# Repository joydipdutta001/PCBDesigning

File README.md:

# PCB Designs ✨✨✨❤
**I am providing some of my work with cad softwares to design PCBs.**
<br></br>
**Software used : ✔ Autodesk EAGLE Educational.**
<br></br>

# Project-1: My own Arduino Designing 😎
[Click Me for Gerber Files](https://github.com/joydipdutta001/PCBDesigning/tree/master/P1-Arduino%20Replica/version1_2020-08-09)
<br></br>
<figure>
    <h3>Schematic</h3>
    
</figure>
<br></br>
    Download Schematic -> (https://github.com/joydipdutta001/PCBDesigning/blob/master/P1-Arduino%20Replica/version1.sch)
<br></br>
<figure>
    <h3>Board</h3>
    
</figure>
<br></br>
     Download Board -> (https://github.com/joydipdutta001/PCBDesigning/blob/master/P1-Arduino%20Replica/version1.brd)
<br></br>

# Project-2: Power Supply and NodeMCU 😎
[Click Me for Gerber Files](https://github.com/joydipdutta001/PCBDesigning/tree/master/P2-NodeMCUandPowerSupply)
<br></br>
<figure>
    <h3>Schematic</h3>
    
</figure>
<br></br>
    Download Schematic -> (https://github.com/joydipdutta001/PCBDesigning/blob/master/P2-NodeMCUandPowerSupply/nodemcuPowerSupply.sch)
<br></br>
<figure>
    <h3>Board</h3>
    
</figure>
<br></br>
     Download Board -> (https://github.com/joydipdutta001/PCBDesigning/blob/master/P2-NodeMCUandPowerSupply/nodemcuPowerSupply.brd)
<br></br>

# Project-3: 4-Channel Relay with 12V PowerSupply 😎
[Click Me for Gerber Files](https://github.com/joydipdutta001/PCBDesigning/tree/master/P3-FourChannelRelayModule)
<br></br>
<figure>
    <h3>Schematic</h3>
    
</figure>
<br></br>
    Download Schematic -> (https://github.com/joydipdutta001/PCBDesigning/blob/master/P3-FourChannelRelayModule/nodemcurelay.sch)
<br></br>
<figure>
    <h3>Board</h3>
    
</figure>
<br></br>
     Download Board -> (https://github.com/joydipdutta001/PCBDesigning/blob/master/P3-FourChannelRelayModule/nodemcurelay.brd)
<br></br>

# Project-4: PCB design of WireLess Display Board with NodeMCU 😎
<br></br>
<figure>
    <h3>Schematic</h3>
    
</figure>
<br></br>

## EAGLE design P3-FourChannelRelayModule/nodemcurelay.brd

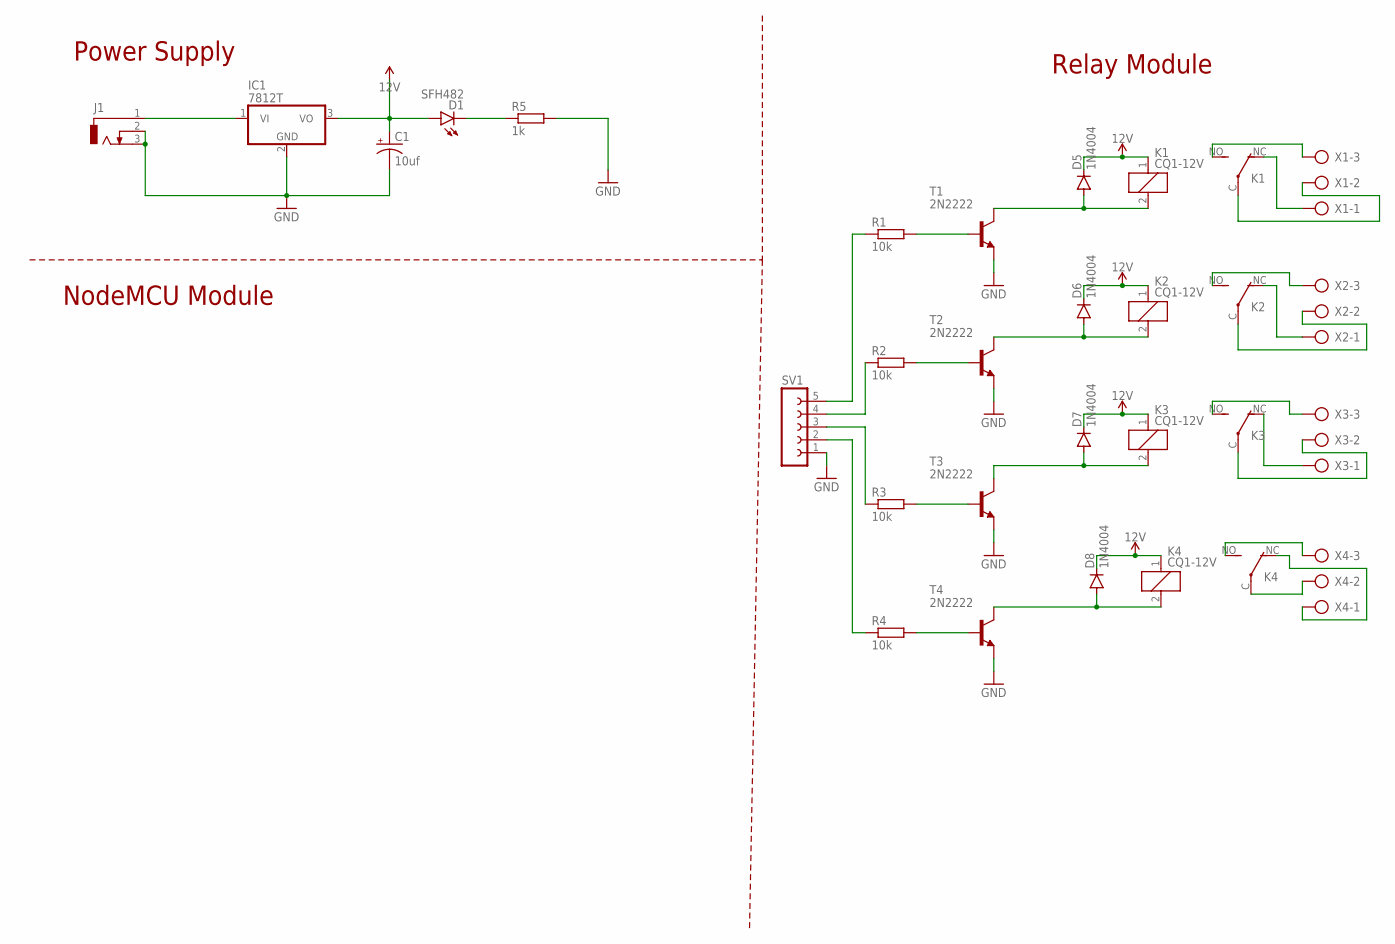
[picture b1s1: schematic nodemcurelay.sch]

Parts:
C1: 10uf; E3,5-8
D1: SFH482
D5, D6, D7, D8: 1N4004; DO41-10
IC1: 7812T; TO220H
J1: DCJ0303
K1, K2, K3, K4: CQ1-12V; CQ1
R1, R2, R3, R4: 10k; 0207/7
R5: 1k; 0207/7
SV1: FE05-1
T1, T2, T3, T4: 2N2222; TO92-EBC-OVAL
X1, X2, X3, X4: AK300/3

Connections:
12V: C1.+, D1.A, D5.C, D6.C, D7.C, D8.C, IC1.3 (VO), K1.1, K2.1, K3.1, K4.1
GND: C1.-, IC1.2 (GND), J1.2, J1.3, R5.2, SV1.1, T1.E, T2.E, T3.E, T4.E
unnamed: R1.2, T1.B
unnamed: R2.2, T2.B
unnamed: R3.2, T3.B
unnamed: R4.2, T4.B
unnamed: IC1.1 (VI), J1.1
unnamed: D5.A, K1.2, T1.C
unnamed: K1.NO (S), X1.3
unnamed: D6.A, K2.2, T2.C
unnamed: D1.K (C), R5.1
unnamed: D7.A, K3.2, T3.C
unnamed: K1.NC (O), X1.1
unnamed: D8.A, K4.2, T4.C
unnamed: R1.1, SV1.5
unnamed: R2.1, SV1.4
unnamed: R3.1, SV1.3
unnamed: R4.1, SV1.2
unnamed: K1.C, X1.2
unnamed: K2.NC (O), X2.1
unnamed: K2.C, X2.2
unnamed: K2.NO (S), X2.3
unnamed: K3.NO (S), X3.3
unnamed: K3.NC (O), X3.1
unnamed: K3.C, X3.2
unnamed: K4.NO (S), X4.3
unnamed: K4.C, X4.2
unnamed: K4.NC (O), X4.1

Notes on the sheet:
Power Supply
Relay Module
NodeMCU Module

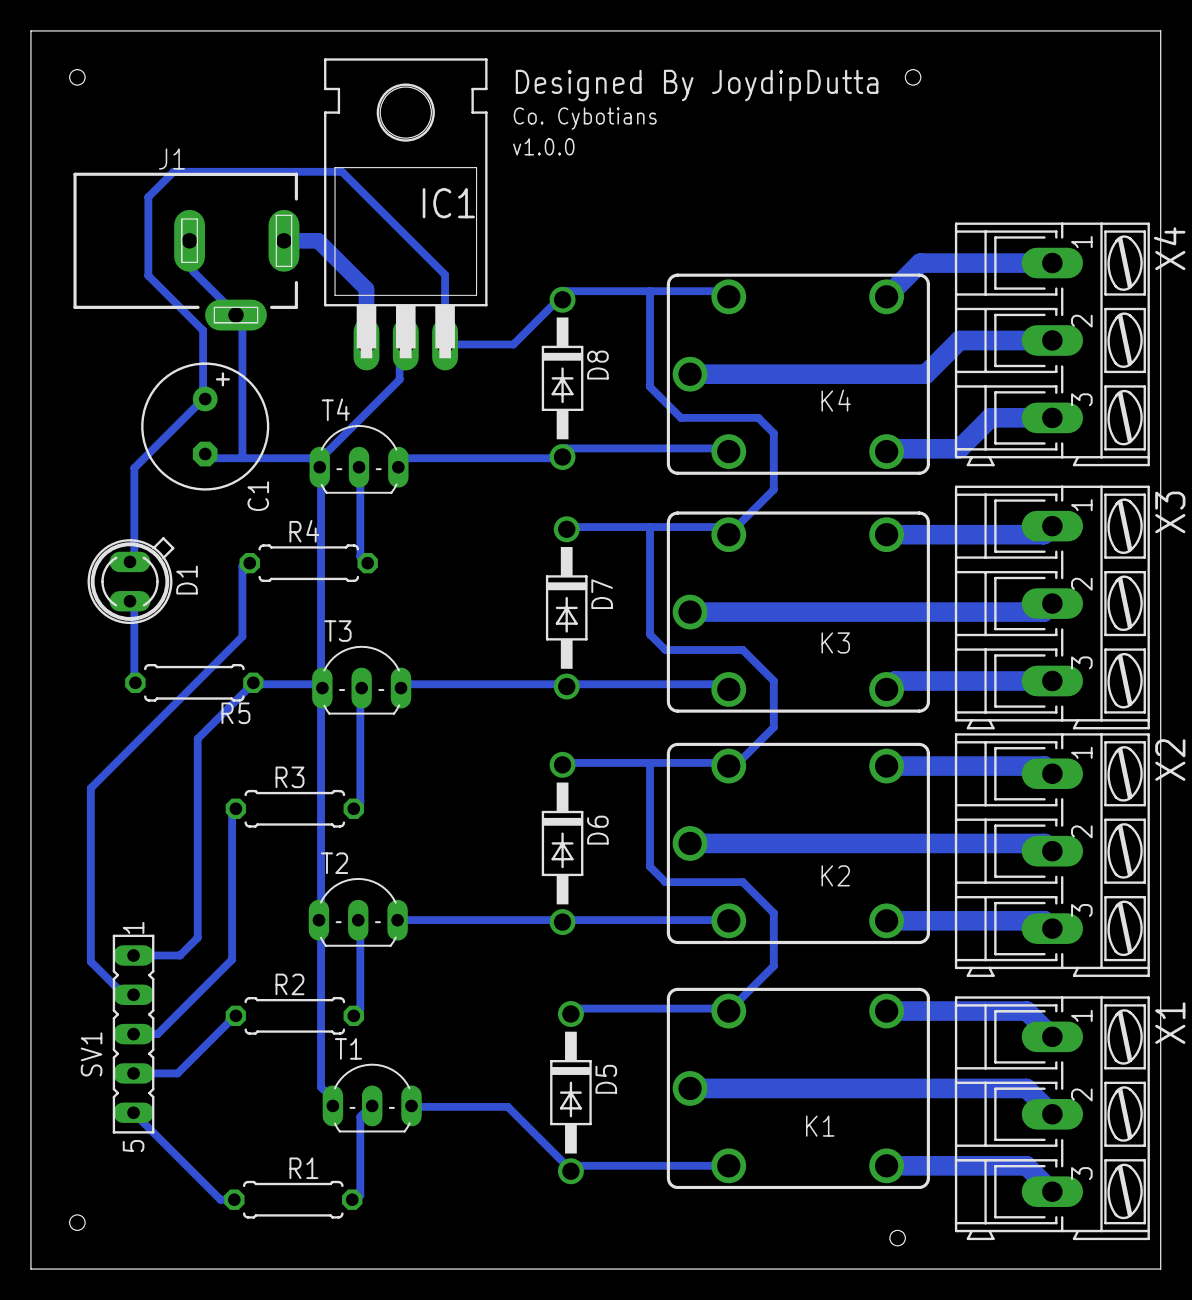
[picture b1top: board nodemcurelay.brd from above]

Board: 2 copper layers, 73.0 x 80.0 mm, 26 parts (0 on the bottom side), 28 nets.

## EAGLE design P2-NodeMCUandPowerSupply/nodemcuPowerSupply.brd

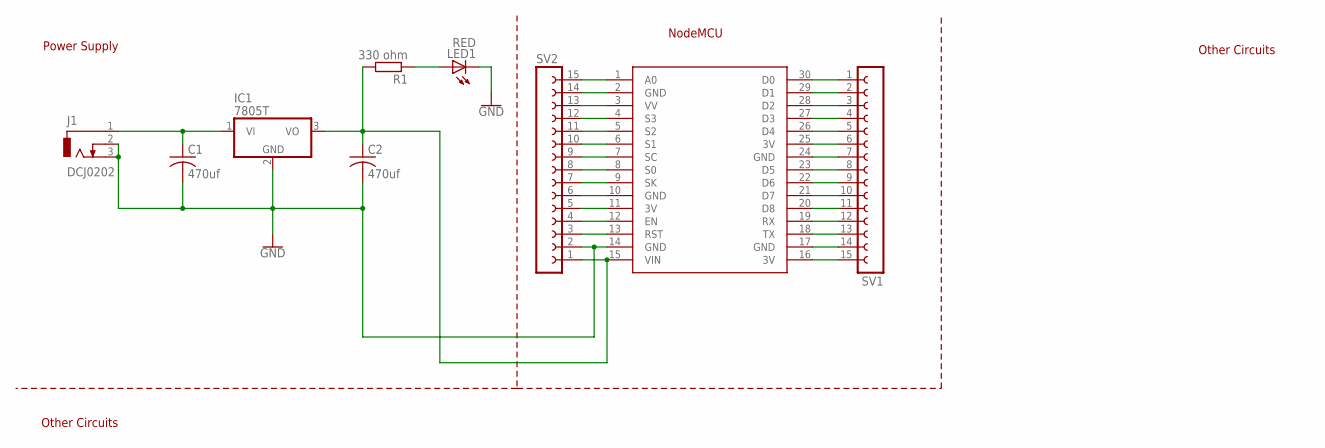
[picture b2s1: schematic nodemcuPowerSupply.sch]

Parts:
C1, C2: 470uf; C025-024X044
IC1: 7805T; TO220H
J1: DCJ0202
LED1: RED; LED3MM
R1: 330 ohm; 0204/5
SV1, SV2: FE15-1; FE15
U$1: NODEMCU

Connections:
GND: C1.2, C2.2, IC1.2 (GND), J1.2, J1.3, LED1.K (C), SV2.2, U$1.14 (GND)
unnamed: SV2.15, U$1.1 (A0)
unnamed: SV2.14, U$1.2 (GND)
unnamed: SV2.13, U$1.3 (VV)
unnamed: SV2.12, U$1.4 (S3)
unnamed: SV2.11, U$1.5 (S2)
unnamed: SV2.10, U$1.6 (S1)
unnamed: SV2.9, U$1.7 (SC)
unnamed: SV2.8, U$1.8 (S0)
unnamed: SV2.7, U$1.9 (SK)
unnamed: SV2.6, U$1.10 (GND)
unnamed: SV2.5, U$1.11 (3V)
unnamed: SV2.4, U$1.12 (EN)
unnamed: SV2.3, U$1.13 (RST)
unnamed: LED1.A, R1.1
unnamed: SV1.1, U$1.30 (D0)
unnamed: SV1.2, U$1.29 (D1)
unnamed: SV1.3, U$1.28 (D2)
unnamed: SV1.4, U$1.27 (D3)
unnamed: SV1.5, U$1.26 (D4)
unnamed: SV1.6, U$1.25 (3V)
unnamed: SV1.7, U$1.24 (GND)
unnamed: SV1.8, U$1.23 (D5)
unnamed: SV1.9, U$1.22 (D6)
unnamed: SV1.10, U$1.21 (D7)
unnamed: SV1.11, U$1.20 (D8)
unnamed: SV1.12, U$1.19 (RX)
unnamed: SV1.13, U$1.18 (TX)
unnamed: SV1.14, U$1.17 (GND)
unnamed: SV1.15, U$1.16 (3V)
unnamed: C1.1, IC1.1 (VI), J1.1
unnamed: C2.1, IC1.3 (VO), R1.2, SV2.1, U$1.15 (VIN)

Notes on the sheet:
Power Supply
NodeMCU
Other Circuits

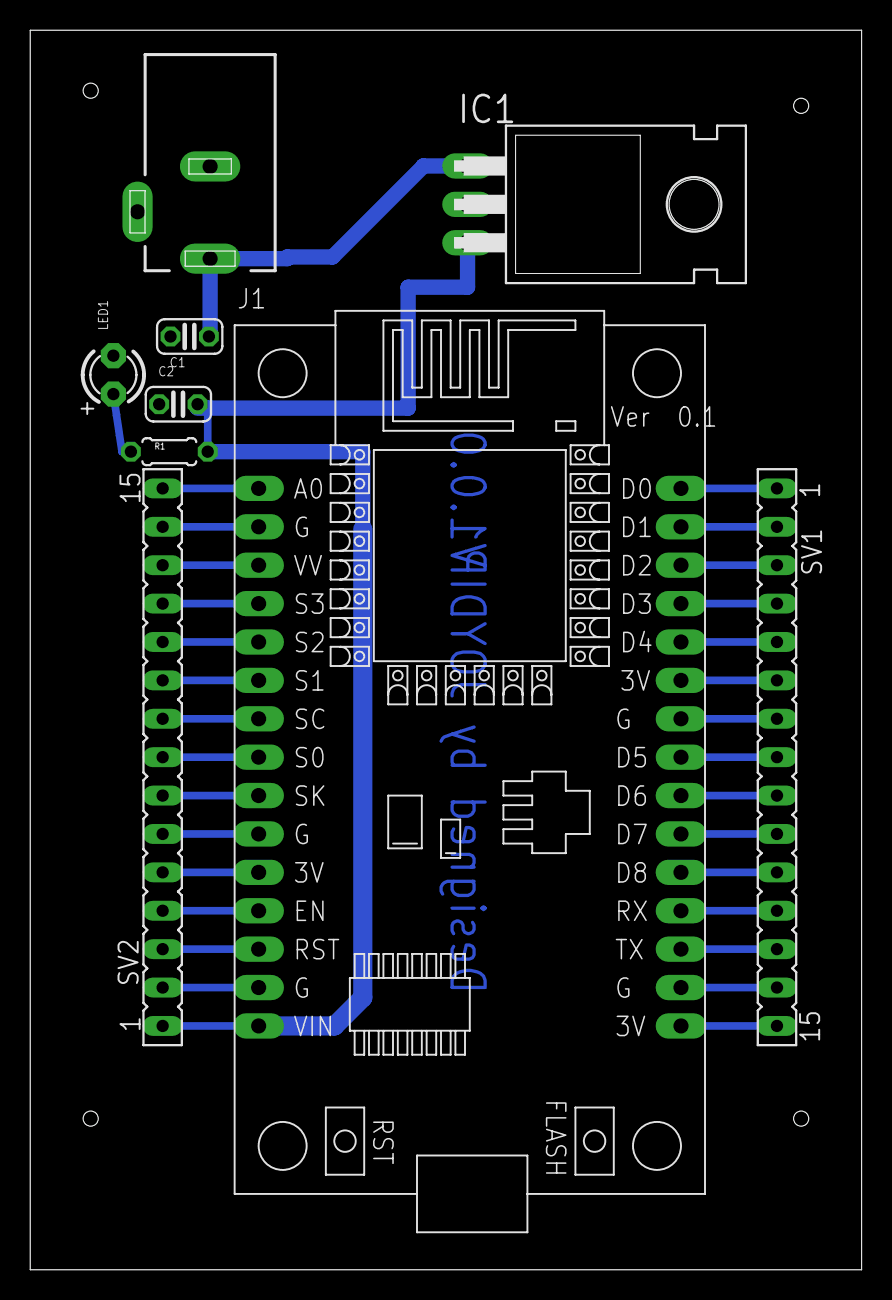
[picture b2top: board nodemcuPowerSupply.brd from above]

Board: 2 copper layers, 55.0 x 82.0 mm, 9 parts (0 on the bottom side), 32 nets.

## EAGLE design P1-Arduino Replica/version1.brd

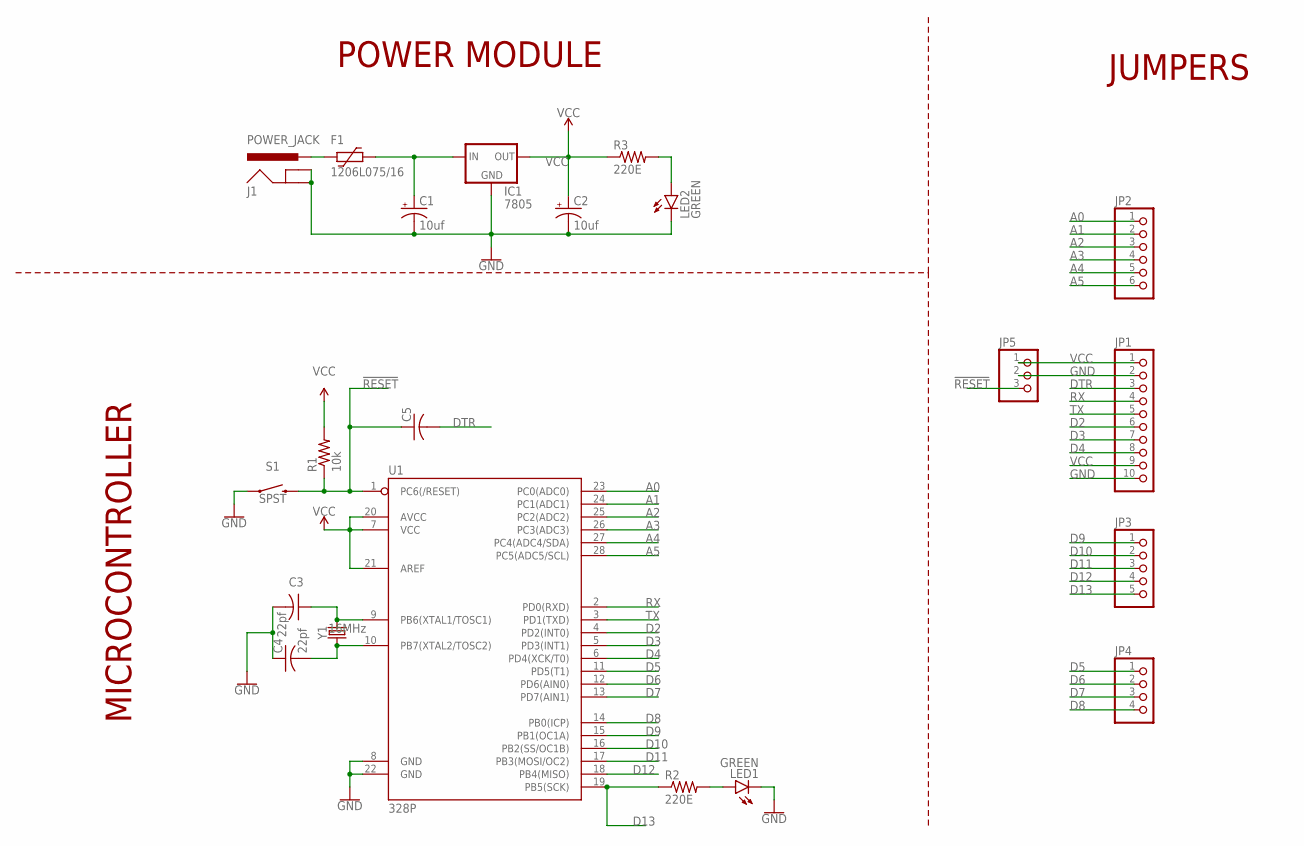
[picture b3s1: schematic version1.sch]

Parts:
C1, C2: 10uf; E2,5-6E
C3, C4: 22pf; C025-024X044
C5: C-US025-024X044; C025-024X044
F1: 1206L075/16; 1206L
IC1: 7805; 78XXS
J1: POWER_JACK; POWER_JACK_PTH
JP1: PINHD-1X10; 1X10
JP2: PINHD-1X6; 1X06
JP3: PINHD-1X5; 1X05
JP4: PINHD-1X4; 1X04
JP5: PINHD-1X3; 1X03
LED1, LED2: GREEN; LED3MM
R1: 10k; 0204/7
R2, R3: 220E; 0204/7
S1: SPST; TACTILE_SWITCH_PTH_6.0MM
U1: 328P; DIP28
Y1: 16MHz; HC49US

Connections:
!RESET: C5.1, JP5.3, R1.1, S1.3 (2), U1.1 (PC6(/RESET))
A0: JP2.1, U1.23 (PC0(ADC0))
A1: JP2.2, U1.24 (PC1(ADC1))
A2: JP2.3, U1.25 (PC2(ADC2))
A3: JP2.4, U1.26 (PC3(ADC3))
A4: JP2.5, U1.27 (PC4(ADC4/SDA))
A5: JP2.6, U1.28 (PC5(ADC5/SCL))
D2: JP1.6, U1.4 (PD2(INT0))
D3: JP1.7, U1.5 (PD3(INT1))
D4: JP1.8, U1.6 (PD4(XCK/T0))
D5: JP4.1, U1.11 (PD5(T1))
D6: JP4.2, U1.12 (PD6(AIN0))
D7: JP4.3, U1.13 (PD7(AIN1))
D8: JP4.4, U1.14 (PB0(ICP))
D9: JP3.1, U1.15 (PB1(OC1A))
D10: JP3.2, U1.16 (PB2(SS/OC1B))
D11: JP3.3, U1.17 (PB3(MOSI/OC2))
D12: JP3.4, U1.18 (PB4(MISO))
D13: JP3.5, R2.1, U1.19 (PB5(SCK))
DTR: C5.2, JP1.3
GND: C1.-, C2.-, C3.2, C4.1, IC1.GND, J1.GND, J1.GNDBREAK, JP1.2, JP1.10, JP5.2, LED1.K (C), LED2.K (C), S1.1, U1.8 (GND), U1.22 (GND)
unnamed: C1.+, F1.1, IC1.IN
unnamed: C3.1, U1.9 (PB6(XTAL1/TOSC1)), Y1.2
unnamed: C4.2, U1.10 (PB7(XTAL2/TOSC2)), Y1.1
unnamed: F1.2, J1.PWR
unnamed: LED2.A, R3.2
unnamed: LED1.A, R2.2
RX: JP1.4, U1.2 (PD0(RXD))
TX: JP1.5, U1.3 (PD1(TXD))
VCC: C2.+, IC1.OUT, JP1.1, JP1.9, JP5.1, R1.2, R3.1, U1.7 (VCC), U1.20 (AVCC), U1.21 (AREF)

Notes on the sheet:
POWER MODULE
JUMPERS
MICROCONTROLLER

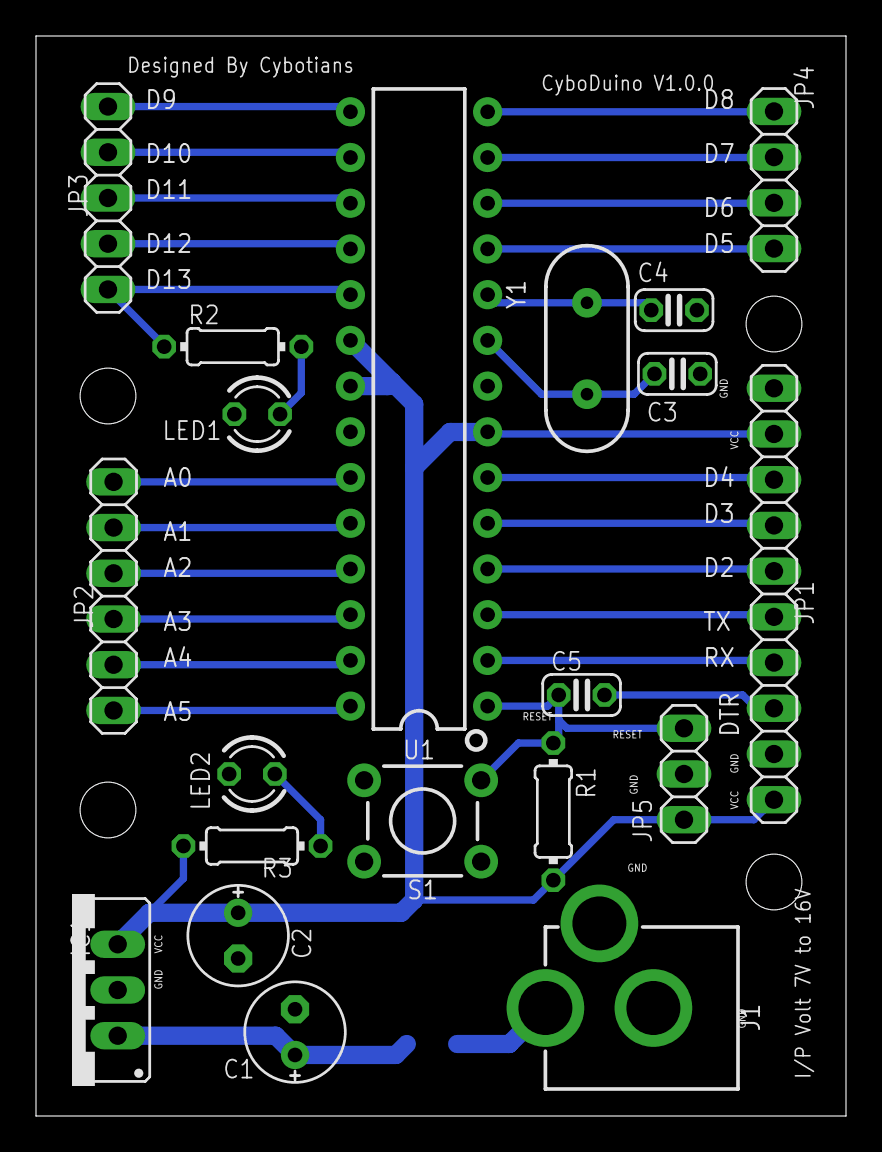
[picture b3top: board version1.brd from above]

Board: 2 copper layers, 45.0 x 60.0 mm, 21 parts (1 on the bottom side), 30 nets.

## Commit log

2020-08-09 Added Project 1
2020-08-09 Added ScreanShots of Project 1
2020-08-09 Added ScreanShots
2020-08-09 Added P2-NodemcuAndPowerSupply
2020-08-10 Deleted Unwanted file
2020-08-10 Added P3-FourChannelRelay
2020-08-11 Updated Relay Boards
2020-08-15 Added P4-WirelessDisplayBoardProject

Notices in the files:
parts and their libraries:
SparkFun-Connectors: Licensing: Creative Commons ShareAlike 4.0 International - https://creativecommons.org/licenses/by-sa/4.0
